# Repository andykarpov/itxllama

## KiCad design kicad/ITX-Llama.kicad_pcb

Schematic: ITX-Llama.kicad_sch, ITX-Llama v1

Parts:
BT1: CR2032; BT_BS-02-A1AJ006; LCSC C964745
C1, C2, C3, C4: 100uF; C_1210_3225Metric; LCSC C90143
C5, C10, C11, C31, C32, C43, C44, C45, C46, C47, C53, C61, C62, C76, C77, C159, C161, C167, C168, C169, C170, C171, C173: 47uF; C_0603_1608Metric; LCSC C140782
C6, C7, C8, C12, C13, C14, C16, C17, C18, C22, C25, C26, C29, C37, C38, C39, C40, C41, C42, C51, C54, C56, C57, C58, C59, C60, C63, C72, C73, C84, C85, C86, C87, C89, C90, C91, C92, C93, C94, C95, C96, C97, C98, C99, C100, C101, C102, C103, C104, C105, C106, C107, C108, C109, C110, C111, C112, C113, C114, C115, C116, C117, C118, C119, C120, C122, C123, C124, C129, C130, C131, C138, C144, C145, C146, C153, C156, C162, C163, C164, C165, C166, C182, C183, C184, C185, C186, C187, C188, C189, C190: 0.1uF; C_0603_1608Metric
C9, C33, C34, C52, C69, C74, C75, C134, C137, C143, C147, C148, C149, C158, C176: 10uF; C_0603_1608Metric
C15, C24, C28, C65, C66, C67, C78, C121, C132, C135, C150, C151, C152, C177, C178: 1uF; C_0603_1608Metric
C19, C23, C35, C36, C125, C126: 1nF; C_0603_1608Metric
C20, C21: 22pF; C_0603_1608Metric
C27: 47uF; C_0603_1608Metric
C30, C68: 2.7nF; C_0603_1608Metric
C48, C49, C50: 330pF; C_0603_1608Metric
C55, C64, C160: 10nF; C_0603_1608Metric
C70, C71: 0.33uF; C_0603_1608Metric
C79, C133, C136, C157: 470pF; C_0603_1608Metric
C80: 1nF; C_1812_4532Metric; Voltage min. 2kV; LCSC C106132
C81, C82, C83: 0.1uF; C_0603_1608Metric; LCSC C14663
C88, C154, C155: 4.7uF; C_0603_1608Metric
C127, C128: 5.6nF; C_0603_1608Metric
C139, C140: 2.2uF; C_0603_1608Metric
C141, C142: 2.2nF; C_0603_1608Metric
C172, C174, C175: 10uF; C_0603_1608Metric; LCSC C140782
C179: 0.1uF; C_0603_1608Metric; LCSC C107004
C180, C181: 30pF; C_0603_1608Metric; LCSC C107004
D1: RGB_LED; D_LED_D5.0mm-4_RGB; LCSC C417349
D2, D3, D4: 1N4148; D_SOD-323F; LCSC C2128
F1, F2, F5, F6, F7: F; Fuse_0603_1608Metric
F3, F4: F; Fuse_0603_1608Metric; LCSC C207017
FB1, FB2: 600Ω@100MHz; R_0603_1608Metric; LCSC C160977
FB3: 50Ω@100MHz; R_1206_3216Metric; LCSC C88997
FB4, FB5, FB6, FB7, FB8, FB9: 70Ω@100MHz; R_0603_1608Metric; LCSC C113031
H1, H2, H3, H4: H_HOLE; H_ATX_PERF
J1: ATX_POWER; J_ATX_5.5mm; LCSC C114125
J2: MICRO_SD; J_MicroSD_TF01A; LCSC C91145
J3: FRONT_PANEL; P_CONN_PANEL; LCSC C492421
J4: PS/2; J_PS2_KMDGX
J5: AGP_3.3V; J_TE_5145263-3
J6: CLICK_VOL; P_CONN_SPKR_VOL
J7: MSC; P_CONN_01X03
J8: COM1; J_DE9M; LCSC C141880
J9: INT_SPKR_VOL; P_CONN_SPKR_VOL
J10: SATA; J_SATA; LCSC C2926809
J11: SPEAKER; P_CONN_01X04; LCSC C492403
J12: MSD; P_CONN_01X03
J14: AUDIO; J_AUDIO_ABA-JAK-027-K24; LCSC C962118
J15: KBC; P_CONN_01X03
J16: KBD; P_CONN_01X03
J17: USB_ETH; J_USB_A_ETH_C3000093; LCSC C3000093
J18: USB_HID; J_USB_A_C456021; LCSC C456021
J19: HID_POWER; P_CONN_01X02
J20: FAN1; J_MOLEX_47053-1000; LCSC C240840
J21: FAN2; J_MOLEX_47053-1000; LCSC C240840
J22: GAMEPORT; J_DA15; LCSC C77835
J23: WAVETABLE; J_CONN_WAVETABLE; LCSC C2884022
J24: PI_ZERO2; J_CONN_RPI_SMD; LCSC C3975165
J25: POWER; P_CONN_01X03
J26: LEFT; P_CONN_01X03
J27: RIGHT; P_CONN_01X03
J28: COM2_TTL; P_CONN_01X03
J29: PI_2/3/4; J_CONN_RPI_SMD_PI3; LCSC C2884029
J30: FAN3; J_MOLEX_47053-1000; LCSC C240840
J31: FAN1_VDD; P_CONN_01X03
J32: FAN2_VDD; P_CONN_01X03
J33: FAN3_VDD; P_CONN_01X03
J34: CD_IN; J_CONN_CD_AUDIO; LCSC C41927
J35: D1_MINI; J_WEMOS_D1_MINI
J36: ESP_POWER; P_CONN_01X02
J38: J_TOSLINK_ZGY133T10; LCSC C277782
J39: LINE_L; P_CONN_01X03
J40: LINE_R; P_CONN_01X03
J41: EXT_SYNTH; J_CONN_02X10
J42: PI_I2C; P_CONN_01X04
J43: I2C; P_CONN_01X04_NO_3D
J46: RP_DEBUG; P_CONN_01X03
L1, L2: L_EMI_FILTER; L_EMI_FILTER_MCM2012B900GBE; LCSC C315725
L3, L4: L_EMI_FILTER; L_EMI_FILTER_MCM2012B900GBE
LOGO1: Llama_logo; LLAMA_LOGO
OUTLINE1: Outline; OUTLINE_PANELIZED
P1: P_SOM-128-EX; P_CONN_SOM-128-EX_FAN; LCSC C2881937
Q1, Q2, Q3, Q4, Q5, Q6, Q7: NPN; Q_BJT_SOT-23-3; LCSC C2146
Q8, Q9, Q10, Q11: Q_NMOS_GDS; Q_NFET_ENH_SOT-23-3; LCSC C255592
R1, R2, R3, R4, R5, R6, R27, R60, R61: 47k; R_0603_1608Metric
R7, R8, R9, R11, R12, R40, R53, R118: 33; R_0603_1608Metric
R10: 0; R_0603_1608Metric
R13, R20, R42, R57, R81, R82, R87, R88, R97, R100, R102, R110, R111, R112, R115, R120: 10k; R_0603_1608Metric
R14, R98, R101: 470; R_0603_1608Metric
R15, R16, R28, R62, R66, R67, R84, R85, R86, R89, R90, R91: 4.7k; R_0603_1608Metric
R17, R63: 600; R_0603_1608Metric
R18, R74, R75, R116: 330; R_0603_1608Metric
R19, R64: 2k; R_0603_1608Metric
R21, R22, R24, R25, R103, R104, R105, R106: 6.8k; R_0603_1608Metric
R23, R26, R29, R30, R31, R32, R33, R34, R35, R36, R37, R38, R41, R46, R47, R48, R49, R50, R51, R52, R54, R79, R80, R108, R121: 5.1k; R_0603_1608Metric
R39, R117: 200; R_0603_1608Metric
R43, R44, R55, R58, R78, R119: 1k; R_0603_1608Metric
R45, R56: 27; R_0603_1608Metric
R59, R94, R95, R96: 470; R_0805_2012Metric; LCSC C17710
R65: 1.43k; R_0603_1608Metric
R68, R69, R76, R77: 75; R_0603_1608Metric
R70, R71, R72, R73: 49.9; R_0603_1608Metric
R83, R107: 3.4k; R_0603_1608Metric
R92, R93: 2.2k; R_0603_1608Metric
R99: 20k; R_0603_1608Metric
R109: 22; R_0603_1608Metric
R113: 15.8k; R_0603_1608Metric
R114: 36k; R_0603_1608Metric
SP1, SP2: SPEAKER; SP; LCSC C252917
SW1: POWER; SW_B3FS-1010; LCSC C271750
SW2: RESET; SW_B3FS-1010; LCSC C271750
SW3: CH559_PRG; SW_B3FS-1010; LCSC C271750
T1: Pulse_H1102NL; T_PULSE_H1102NL; LCSC C18584
U1: MAX16054; U_TSOT-23-6; LCSC C79401
U2: U_74LVC1G04; U_SOT-23-5; LCSC C7827
U3: U_CS4237B-KQ; U_TQFP-100_14x14mm_P0.5mm_HandSoldering
U4: GD75232; U_TSSOP-20_4.4x6.5mm_P0.65mm; LCSC C543039
U5: U_MC33078; SOIC-8_3.9x4.9mm_P1.27mm; LCSC C108206
U6: PI7C9X118SL; U_LQFP-128_14x14mm_P0.4mm_EP
U7: AP7165; U_Diodes_SO-8EP; LCSC C460364
U8, U10, U13, U14: U_MIC5219-3.3YM5; U_SOT-23-5; LCSC C29613
U9: U_ATTINY84A; U_DIP-14_W7.62mm
U11: EMC2303; U_EMC2303; LCSC C621414
U12: PCM5102A; U_TSSOP-20_4.4x6.5mm_P0.65mm; LCSC C107671
U15: W25Q32JVSS; U_SOIC-8_5.23x5.23mm_P1.27mm
U16: U_74LVC1G126; U_SOT-23-5; LCSC C7834
U17: U_RP2040; U_QFN40P700X700X90-57N
X1: 16.9344MHz; X_Crystal_SMD_HC49S-MINI; LCSC C4944017
X2: 12MHz; X_SMD3225; LCSC C9002

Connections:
+1.8V: FB3.1, P1.A56 (VCC1.8_OUT)
+1.15V: C75.2, C153.2, FB6.1, FB7.1, R113.1, U7.7 (VOUT), U7.8 (VOUT)
+1.15V_VDDA: C101.2, C102.2, C155.2, FB7.2, U6.15 (VDDA), U6.18 (VDDA)
+1.15V_VDDC: C89.2, C90.2, C91.2, C92.2, C93.2, C94.2, C95.2, C96.2, C97.2, C98.2, C99.2, C100.2, C154.2, FB6.2, U6.7 (VDDCAUX), U6.30 (VDDC), U6.35 (VDDC), U6.45 (VDDC), U6.53 (VDDC), U6.62 (VDDC), U6.73 (VDDC), U6.81 (VDDC), U6.95 (VDDC), U6.105 (VDDC), U6.114 (VDDC), U6.127 (VDDC)
+3.3V: C3.1, C7.1, C12.1, C22.2, C74.2, C122.1, FB4.1, FB5.1, FB8.1, FB9.1, J1.1 (+3.3V), J1.2 (+3.3V), J1.12 (+3.3V), J1.13 (+3.3V), J2.4 (VDD), R1.1, R2.1, R3.1, R4.1, R5.1, R6.1, R74.1, R75.1, R79.1, R80.1, R84.2, R85.2, R86.2, R87.1, R88.1, R95.1, R102.1, R120.2, U2.5 (VCC), U3.45 (VD1), U7.1 (VIN), U7.2 (VIN), U7.4 (EN), U11.3 (VDD)
+3.3VSB: C156.2, C158.1, U9.1 (VCC), U10.5 (OUT)
+3.3V_118SL: C103.2, C104.2, C105.2, C106.2, C107.2, C108.2, C109.2, C110.2, C111.2, C112.2, C113.2, C114.2, C115.2, C116.2, C117.2, C118.2, C119.2, FB4.2, R33.2, R34.2, R36.1, R37.1, R38.1, R51.1, R52.1, R54.1, R108.2, R121.2, U6.2 (VAUX), U6.25 (VD33), U6.38 (VD33), U6.50 (VD33), U6.55 (VD33), U6.58 (VD33), U6.66 (VD33), U6.72 (VD33), U6.77 (VD33), U6.82 (VD33), U6.87 (VD33), U6.91 (VD33), U6.101 (VD33), U6.107 (VD33), U6.112 (VD33), U6.118 (VD33), U6.123 (VD33)
+3.3V_PCM_A: C137.1, C143.1, C144.1, U12.8 (AVDD), U14.5 (OUT)
+3.3V_PCM_D: C134.1, C138.1, C145.1, C147.1, C148.1, U12.1 (CPVDD), U12.17 (XSMT), U12.20 (DVDD), U13.5 (OUT)
+3.3V_VDDA: C88.2, C120.2, FB5.2, U6.10 (VDDA33)
+5VA: C25.1, C72.1, FB1.2, U3.81 (VA), U5.8 (VCC)
+5VFILT: C13.2, C14.2, C16.2, C18.2, FB2.2, U3.17 (VDF1), U3.54 (VDF4), U3.65 (VDF2), U3.98 (VDF3)
+5VSB: C8.2, C121.1, D1.2 (A), J1.9 (+5VSB), R59.1, U1.6 (VCC), U10.1 (IN), U10.3 (EN)
+12V: C1.1, C51.2, C52.2, C172.1, C174.1, C175.1, J1.10 (+12V), J1.11 (+12V), J5.A1 (+12V), J23.18 (+12V), J31.1, J32.1, J33.1, R96.1, U4.1 (VDD)
-12V: C4.2, J1.14 (-12V), J23.22 (-12V), U4.10 (VSS)
/3.3V_MIDI_OUT: J24.10 (BCM15/RDX), J29.10 (BCM15/RDX), R99.1, R100.2
/A0: P1.B3 (GP70), U3.25 (SA0)
/A1: P1.B4 (GP71), U3.26 (SA1)
/A2: P1.B5 (GP72), U3.27 (SA2)
/A3: P1.B6 (GP73), U3.28 (SA3)
/A4: P1.B7 (GP74), U3.29 (SA4)
/A5: P1.B8 (GP75), U3.30 (SA5)
/A6: P1.B9 (GP76), U3.31 (SA6)
/A7: P1.B10 (GP77), U3.32 (SA7)
/A8: P1.B11 (GP60), U3.33 (SA8)
/A9: P1.B12 (GP61), U3.34 (SA9)
/A10: P1.B13 (GP62), U3.35 (SA10)
/A11: P1.B14 (GP63), U3.36 (SA11)
/A12: P1.B15 (GP64), U3.94 (SA12)
/A13: P1.B16 (GP65), U3.93 (SA13)
/A14: P1.B17 (GP66), U3.92 (SA14)
/A15: P1.B18 (GP67), U3.91 (SA15)
/AD_STB0: J5.B59 (AD_STB0), R26.2
/AD_STB1: J5.B32 (AD_STB1), R29.2
/AEN: P1.B33 (GP44), U3.39 (AEN)
/AUDIO_L_PI: C141.2, J26.3, R98.2
/AUDIO_L_WT: J23.24 (AUDIO_L), J26.1
/AUDIO_R_PI: C142.2, J27.3, R101.2
/AUDIO_R_WT: J23.20 (AUDIO_R), J27.1
/AUDIO_VREF: R60.2, U3.78 (VREF)
/BOOTSEL: R43.2, SW3.1 (A)
/CTS1: P1.A10 (GP07), U4.14 (RY4)
/D0: P1.B47 (GP20), U3.41 (SD0)
/D1: P1.B48 (GP21), U3.42 (SD1)
/D2: P1.B49 (GP22), U3.43 (SD2)
/D3: P1.B50 (GP23), U3.44 (SD3)
/D4: P1.B51 (GP24), U3.47 (SD4)
/D5: P1.B52 (GP25), U3.48 (SD5)
/D6: P1.B53 (GP26), U3.49 (SD6)
/D7: P1.B54 (GP27), U3.50 (SD7)
/DCD1: P1.A3 (GP00), U4.19 (RY1)
/DRQ1: P1.B27 (GP56), U3.51 (DRQB(DRQ1*))
/DSR1: P1.A9 (GP06), U4.18 (RY2)
/DTR1: P1.A8 (GP05), U4.13 (DA3)
/FM_A0: J41.18, U3.14 (SCL/XA0)
/FM_A1: J41.16, U3.13 (XA1)
/FM_D0: J41.12, U3.8 (SDA/XD0)
/FM_D1: J41.11, U3.7 (XD1/SCLK)
/FM_D2: J41.10, U3.6 (XD2/SDIN)
/FM_D3: J41.9, U3.5 (XD3/SDOUT)
/FM_D4: J41.8, U3.4 (XD4/FSYNC)
/FM_D5: J41.7, U3.3 (XD5/MCLK)
/FM_D6: J41.6, U3.2 (XD6/LRCK)
/FM_D7: J41.5, U3.1 (XD7/SDATA)
/FM_SYNTH_L: C24.2, J41.1
/FM_SYNTH_R: C28.2, J41.2
/HDD_LED+: J3.1, R116.2
/HDD_LED-: J3.2, Q6.3 (C)
/HID_VCC: C78.1, F5.1, F6.1, J19.2, U8.1 (IN), U8.3 (EN)
/I2S_BCLK: J24.12 (BCM18/PWM0), J29.12 (BCM18/PWM0), U12.13 (BCK)
/I2S_DATA: J24.40 (BCM21/SCLK), J29.40 (BCM21/SCLK), U12.14 (DIN)
/I2S_LRCLK: J24.35 (BCM19/MISO), J29.35 (BCM19/MISO), U12.15 (LRCK)
/INT_MIDI_L: J26.2, J39.1
/INT_MIDI_R: J27.2, J40.1
/IOCHRDY: P1.B34 (GP45), U3.40 (IOCHRDY)
/IRQ7: P1.B21 (GP50), U3.23 ((INT7*)IRQB)
/JAB1: C126.2, J22.2, R91.2, U3.70 (JAB1)
/JAB2: C125.2, J22.7, R90.2, U3.61 (JAB2)
/JACX: C128.2, R92.2, U3.68 (JACX)
/JACX_: J22.3, R92.1
/JACY: C127.2, R93.2, U3.63 (JACY)
/JACY_: J22.6, R93.1
/KBCLK: J15.2, P1.A12 (GP91), R66.1
/KBDATA: J16.2, P1.A14 (GP93), R67.1
/LAN_RD+: P1.A54 (LAN_RX+), R72.2, T1.6 (RD+)
/LAN_RD-: P1.A52 (LAN_RX-), R73.2, T1.8 (RD-)
/LAN_TD+: P1.A53 (LAN_TX+), R70.2, T1.1 (TD+)
/LAN_TD-: P1.A51 (LAN_TX-), R71.2, T1.3 (TD-)
/LIN: J14.10, J14.11, J39.3
/LINE_IN_L: J39.2, R21.1
/LINE_IN_R: J40.2, R24.1
/LMIC: C73.1, J14.2, J14.3
/LOUT: C34.2, J14.6, J14.7
/M66EN: R121.1, U6.102 (M66EN)
/MIDI_IN: J22.15, R89.2, U3.59 (MIDIN)
/MIDI_OUT: J22.12, J23.4 (MIDI_IN), R100.1, U3.60 (MIDOUT)
/MSCLK: J7.2, P1.A13 (GP92), R15.1
/MSDATA: J12.2, P1.A15 (GP94), R16.1
/PAR: J5.A50 (PAR), U6.94 (PAR)
/PCI_AD0: J5.A65 (AD[0]), U6.64 (AD0)
/PCI_AD1: J5.B65 (AD[1]), U6.67 (AD1)
/PCI_AD2: J5.A63 (AD[2]), U6.69 (AD2)
/PCI_AD3: J5.B63 (AD[3]), U6.68 (AD3)
/PCI_AD4: J5.A62 (AD[4]), U6.70 (AD4)
/PCI_AD5: J5.B62 (AD[5]), U6.71 (AD5)
/PCI_AD6: J5.A60 (AD[6]), U6.74 (AD6)
/PCI_AD7: J5.B60 (AD[7]), U6.75 (AD7)
/PCI_AD8: J5.B57 (AD[8]), U6.78 (AD8)
/PCI_AD9: J5.A56 (AD[9]), U6.79 (AD9)
/PCI_AD10: J5.B56 (AD[10]), U6.80 (AD10)
/PCI_AD11: J5.A54 (AD[11]), U6.83 (AD11)
/PCI_AD12: J5.B54 (AD[12]), U6.85 (AD12)
/PCI_AD13: J5.A53 (AD[13]), U6.86 (AD13)
/PCI_AD14: J5.B53 (AD[14]), U6.88 (AD14)
/PCI_AD15: J5.A51 (AD[15]), U6.90 (AD15)
/PCI_AD16: J5.A39 (AD[16]), U6.104 (AD16)
/PCI_AD17: J5.B38 (AD[17]), U6.103 (AD17)
/PCI_AD18: J5.A38 (AD[18]), U6.106 (AD18)
/PCI_AD19: J5.B36 (AD[19]), U6.108 (AD19)
/PCI_AD20: J5.A36 (AD[20]), U6.109 (AD20)
/PCI_AD21: J5.B35 (AD[21]), U6.110 (AD21)
/PCI_AD22: J5.A35 (AD[22]), U6.111 (AD22)
/PCI_AD23: J5.B33 (AD[23]), U6.113 (AD23)
/PCI_AD24: J5.A30 (AD[24]), U6.117 (AD24)
/PCI_AD25: J5.B30 (AD[25]), U6.119 (AD25)
/PCI_AD26: J5.A29 (AD[26]), U6.120 (AD26)
/PCI_AD27: J5.B29 (AD[27]), U6.122 (AD27)
/PCI_AD28: J5.A27 (AD[28]), U6.121 (AD28)
/PCI_AD29: J5.B27 (AD[29]), U6.124 (AD29)
/PCI_AD30: J5.A26 (AD[30]), U6.126 (AD30)
/PCI_AD31: J5.B26 (AD[31]), U6.125 (AD31)
/PCI_CLK0: J5.B7 (CLK), R109.1
/PE0_CLK+: C85.2, P1.A45 (PE0_CLK-)
/PE0_CLK+_: C85.1, U6.13 (REFCLKP)
/PE0_CLK-: C84.2, P1.A47 (PE0_CLK+)
/PE0_CLK-_: C84.1, U6.12 (REFCLKN)
/PE0_RX+: C87.2, P1.A44 (PE0_RX+)
/PE0_RX+_: C87.1, U6.17 (TP)
/PE0_RX-: C86.2, P1.A42 (PE0_RX-)
/PE0_RX-_: C86.1, U6.16 (TN)
/PE0_TX+: P1.A41 (PE0_TX-), U6.21 (RP)
/PE0_TX-: P1.A43 (PE0_TX+), U6.20 (RN)
/PI7_SCL: R80.2, U6.3 (SCL)
/PI7_SDA: R79.2, U6.5 (SDA)
/PI_SCL: J24.5 (BCM3/SCL), J29.5 (BCM3/SCL), J42.3 (SCL)
/PI_SDA: J24.3 (BCM2/SDA), J29.3 (BCM2/SDA), J42.4 (SDA)
/PS2_KBCLK: J4.A5 (KBCLK), J15.3
/PS2_KBDATA: J4.A1 (KBDATA), J16.3
/PS2_MSCLK: J4.B5 (MSCLK), J7.3
/PS2_MSDATA: J4.B1 (MSDATA), J12.3
/PWM1: J20.4 (PWM), U11.5 (PWM1)
/PWM2: J21.4 (PWM), U11.7 (PWM2)
/PWM3: J30.4 (PWM), U11.11 (PWM3)
/PWM_CLICK: R119.1, U9.8 (PCINT5/OC1B/PA5)
/PWM_GREEN: R82.1, U9.10 (PCINT3/PA3)
/PWM_HDD: R115.1, U9.12 (PCINT1/PA1)
/PWM_PWR: R20.1, U9.13 (PCINT0/PA0)
/PWM_RED: R81.1, U9.11 (PCINT2/PA2)
/PWR_LED+: J3.8, R18.2
/PWR_LED-: J3.7, Q7.3 (C)
/QSPI_CS: R42.1, R43.1, U15.1 (~CS), U17.56 (QSPI_CSN)
/QSPI_SCK: U15.6 (CLK), U17.52 (QSPI_SCLK)
/QSPI_SD0: U15.5 (DI(IO0)), U17.53 (QSPI_SD0)
/QSPI_SD1: U15.2 (DO(IO1)), U17.55 (QSPI_SD1)
/QSPI_SD2: U15.3 (IO2), U17.54 (QSPI_SD2)
/QSPI_SD3: U15.7 (IO3), U17.51 (QSPI_SD3)
/RI1: P1.A6 (GP03), U4.12 (RY5)
/RIN: J14.12, J14.13, J40.3
/RMIC: J14.4, J14.5, R64.2
/ROUT: C33.2, J14.8, J14.9
/RP_RX: J46.3, U17.16 (GPIO13)
/RP_TX: J46.1, U17.15 (GPIO12)
/RSTDRV: U2.4, U3.90 (RESDRV)
/RS_CTS1: J8.8, U4.7 (RA4)
/RS_DCD1: J8.1, U4.2 (RA1)
/RS_DSR1: J8.6, U4.3 (RA2)
/RS_DTR1: C50.2, J8.4, U4.8 (DY3)
/RS_RI1: J8.9, U4.9 (RA5)
/RS_RTS1: C48.2, J8.7, U4.5 (DY1)
/RS_RX1: J8.2, U4.4 (RA3)
/RS_TX1: C49.2, J8.3, U4.6 (DY2)
/RTS1: P1.A5 (GP02), U4.16 (DA1)
/RX1: P1.A7 (GP04), U4.17 (RY3)
/RX2: J28.3, J35.16 (TX/GPIO1), P1.B63 (GP16), U9.2 (PB0/PCINT8)
/SATA_RX+: J10.6 (B+), P1.A40 (SATA_RX+)
/SATA_RX-: J10.5 (B-), P1.A38 (SATA_RX-)
/SATA_TX+: J10.2 (A+), P1.A39 (SATA_TX+)
/SATA_TX-: J10.3 (A-), P1.A37 (SATA_TX-)
/SB_STB: J5.B18 (SB_STB), R30.2
/SD_CD: J2.9 (CD), P1.A63 (GP86), R1.2
/SD_CLK: P1.A60 (GP83), R10.2
/SD_CMD: P1.A59 (GP82), R9.2, U9.5 (PB2/PCINT10/INT0/OC0A)
/SD_DAT0: P1.A61 (GP84), R11.2, U9.6 (PA7/PCINT7/OC0B)
/SD_DAT1: P1.A62 (GP85), R12.2
/SD_DAT2: P1.A57 (GP80), R7.2
/SD_DAT3: P1.A58 (GP81), R8.2
/SPDIF_OUT: U3.67 (JBCX*/SDOUT), U16.2
/SPKR: P1.B58 (GP11), R27.1, R44.1, R55.1
/TACH1: J20.3 (TACH), R88.2, U11.6 (TACH1)
/TACH2: J21.3 (TACH), R87.2, U11.8 (TACH2)
/TACH3: J30.3 (TACH), R102.2, U11.12 (TACH3)
/TX1: P1.A4 (GP01), U4.15 (DA2)
/TX2: J28.1, J35.15 (RX/GPIO3), P1.B61 (GP14), U9.3 (PB1/PCINT9)
/USBD1+: L1.3, P1.A23 (USBD1+)
/USBD1-: L1.2, P1.A21 (USBD1-)
/USBD2+: L2.3, P1.A24 (USBD2+)
/USBD2-: L2.2, P1.A22 (USBD2-)
/USBDX1+: J17.U3 (D1+), L1.4
/USBDX1-: J17.U2 (D1-), L1.1
/USBDX2+: J17.U7 (D2+), L2.4
/USBDX2-: J17.U6 (D2-), L2.1
/USBHID1+: L3.3, R45.1
/USBHID1-: L3.2, R56.1
/USBHID2+: L4.3, U17.36 (GPIO24)
/USBHID2-: L4.2, U17.37 (GPIO25)
/USBHIDX1+: J18.7 (D2+), L3.4
/USBHIDX1-: J18.6 (D2-), L3.1
/USBHIDX2+: J18.3 (D1+), L4.4
/USBHIDX2-: J18.2 (D1-), L4.1
/USB_KBCLK_HV: J15.1, Q9.2 (D)
/USB_KBCLK_LV: Q9.3 (S), R110.2, U17.5 (GPIO3)
/USB_KBDATA_HV: J16.1, Q8.2 (D)
/USB_KBDATA_LV: Q8.3 (S), R97.2, U17.4 (GPIO2)
/USB_MSCLK_HV: J7.1, Q10.2 (D)
/USB_MSCLK_LV: Q10.3 (S), R111.2, U17.7 (GPIO5)
/USB_MSDATA_HV: J12.1, Q11.2 (D)
/USB_MSDATA_LV: Q11.3 (S), R112.2, U17.6 (GPIO4)
/V86_SCL: J43.3 (SCL), P1.B62 (GP15), R85.1, U9.9 (PCINT4/SCL/PA4), U11.2 (SMCLK)
/V86_SDA: J43.4 (SDA), P1.B60 (GP13), R84.1, U9.7 (PA6/PCINT6/OCA1A/SDA), U11.1 (SMDATA)
/VBATT: BT1.1 (+), P1.A55 (VBATT)
/X_SD_CLK: J2.5 (CLK), R10.1
/X_SD_CMD: J2.3 (CMD), R4.2, R9.1
/X_SD_DAT0: J2.7 (DAT0), R3.2, R11.1
/X_SD_DAT1: J2.8 (DAT1), R2.2, R12.1
/X_SD_DAT2: J2.1 (DAT2), R6.2, R7.1
/X_SD_DAT3: J2.2 (DAT3/CD), R5.2, R8.1
/~BRESET: J23.26 (~RESET), J41.4, U3.15 (~BRESET)
/~CBE0: J5.A57 (~C/BE[0]), U6.76 (~CBE0)
/~CBE1: J5.B51 (~C/BE[1]), U6.89 (~CBE1)
/~CBE2: J5.B39 (~C/BE[2]), U6.99 (~CBE2)
/~CBE3: J5.A33 (~C/BE[3]), U6.116 (~CBE3)
/~DACK1: P1.B28 (GP57), U3.56 (~DACKB(~DACK1*))
/~DEVSEL: J5.B46 (~DEVSEL), R49.2, U6.98 (~DEVSEL)
/~FM_CS: J41.13, U3.9 (~SCS/~UP)
/~FM_RD: J41.14, U3.10 (~XIOR)
/~FM_WR: J41.15, U3.11 (~XIOW)
/~FRAME: J5.A41 (~FRAME), R46.2, U6.63 (~FRAME)
/~GNT0: J5.A8 (~GNT), R41.2, U6.37 (~GNT0)
/~INTA: J5.A6 (~INTA), R31.2, U6.36 (~INTA)
/~INTB: J5.B6 (~INTB), R32.2, U6.43 (~INTB)
/~INTC: R33.1, U6.57 (~INTC)
/~INTD: R34.1, U6.60 (~INTD)
/~IOR: P1.B40 (GP31), U3.37 (~IOR)
/~IOW: P1.B39 (GP30), U3.38 (~IOW)
/~IRDY: J5.B41 (~IRDY), R48.2, U6.97 (~IRDY)
/~LAN_DUPLEX: J17.D2, P1.B57 (GP10)
/~LAN_LINK_ACK: J17.D4, P1.B59 (GP12)
/~LOCK: R51.2, U6.93 (~LOCK)
/~PCIE_RST: P1.A46 (~PCIRST), U2.2, U6.29 (~PERST)
/~PCI_RST: J5.A7 (~RST), U6.46 (~RESET)
/~PERR: R52.2, U6.92 (~PERR)
/~PIPE: J5.A12 (~PIPE), R23.2
/~PS_ON: J1.16 (~PS_ON), U1.4 (~OUT)
/~PWR_SW: J3.6, SW1.2 (B), U1.1 (IN)
/~REQ0: J5.B8 (~REQ), R35.2, U6.31 (~REQ0)
/~RST_SIG: C9.1, P1.A48 (~RESET), R14.1
/~RST_SW: J3.3, R13.2, R14.2, SW2.2 (B)
/~SERR: R54.2, U6.61 (~SERR)
/~STOP: J5.A47 (~STOP), R50.2, U6.96 (~STOP)
/~TRDY: J5.A46 (~TRDY), R47.2, U6.100 (~TRDY)
GND: BT1.2 (-), C1.2, C2.2, C3.2, C4.1, C5.2, C6.2, C7.2, C8.1, C9.2, C10.1, C11.1, C12.2, C13.1, C14.1, C15.2, C16.1, C17.2, C18.1, C19.2, C20.1, C21.1, C22.1, C23.2, C25.2, C26.1, C27.1, C30.2, C31.2, C32.2, C35.2, C36.2, C37.1, C38.1, C39.1, C40.1, C41.1, C42.1, C43.2, C44.2, C45.2, C46.2, C47.2, C48.1, C49.1, C50.1, C51.1, C52.1, C53.2, C54.1, C55.2, C56.1, C57.1, C58.1, C59.1, C60.1, C61.2, C62.2, C63.1, C64.2, C67.1, C69.2, C72.2, C74.1, C75.1, C76.2, C77.2, C78.2, C79.2, C80.1, C81.1, C82.1, C83.1, C88.1, C89.1, C90.1, C91.1, C92.1, C93.1, C94.1, C95.1, C96.1, C97.1, C98.1, C99.1, C100.1, C101.1, C102.1, C103.1, C104.1, C105.1, C106.1, C107.1, C108.1, C109.1, C110.1, C111.1, C112.1, C113.1, C114.1, C115.1, C116.1, C117.1, C118.1, C119.1, C120.1, C121.2, C122.2, C123.1, C124.1, C125.1, C126.1, C127.1, C128.1, C129.1, C130.1, C131.1, C132.2, C133.2, C134.2, C135.2, C136.2, C137.2, C138.2, C139.1, C141.1, C142.1, C143.2, C144.2, C145.2, C146.1, C147.2, C148.2, C149.1, C153.1, C154.1, C155.1, C156.1, C157.2, C158.2, C159.2, C160.2, C161.2, C162.1, C163.2, C164.1, C165.1, C166.1, C167.2, C168.2, C169.2, C170.2, C171.2, C172.2, C173.2, C174.2, C175.2, C176.2, C177.2, C178.2, C179.1, C180.2, C181.2, C182.1, C183.1, C184.1, C185.1, C186.1, C187.1, C188.1, C189.1, C190.1, H1.1, H2.1, H3.1, H4.1, J1.3 (GND), J1.5 (GND), J1.7 (GND), J1.15 (GND), J1.17 (GND), J1.18 (GND), J1.19 (GND), J1.24 (GND), J2.6 (VSS), J2.S (Shield), J3.4, J3.5, J4.A3 (GND), J4.B3 (GND), J4.S (SHIELD), J5.A3 (RES_GND), J5.A5 (GND), J5.A13 (GND), J5.A19 (GND), J5.A31 (GND), J5.A37 (GND), J5.A43 (GND), J5.A49 (GND), J5.A55 (GND), J5.A61 (GND), J5.B5 (GND), J5.B13 (GND), J5.B19 (GND), J5.B31 (GND), J5.B37 (GND), J5.B43 (GND), J5.B49 (GND), J5.B55 (GND), J5.B61 (GND), J8.5, J8.10 (GND), J8.11 (GND), J10.1 (GND), J10.4 (GND), J10.7 (GND), J11.3, J14.1, J17.U4 (GND1), J17.U8 (GND2), J18.4 (GND1), J18.8 (GND2), J18.S (Shield), J20.1 (GND), J21.1 (GND), J22.4, J22.5, J22.S (SHIELD), J23.1 (GND), J23.3 (GND), J23.5 (GND), J23.7 (GND), J23.9 (GND), J23.11 (GND), J23.15 (AGND), J23.17 (AGND), J23.19 (AGND), J23.21 (AGND), J23.23 (AGND), J23.25 (AGND), J24.6 (GND), J24.9 (GND), J24.14 (GND), J24.20 (GND), J24.25 (GND), J24.30 (GND), J24.34 (GND), J24.39 (GND), J28.2, J29.6 (GND), J29.9 (GND), J29.14 (GND), J29.20 (GND), J29.25 (GND), J29.30 (GND), J29.34 (GND), J29.39 (GND), J30.1 (GND), J35.10 (GND), J38.3 (GND), J41.3, J41.20, J42.1 (GND), J43.1 (GND), J46.2, P1.A2 (GND), P1.A19 (GND), P1.A20 (GND), P1.A25 (AGND), P1.A26 (AGND), P1.A35 (GND), P1.A36 (GND), P1.A49 (GND), P1.A50 (GND), P1.A64 (GP87), P1.B19 (GND), P1.B20 (GND), P1.B37 (GND), P1.B38 (GND), P1.B55 (GND), P1.B56 (GND), Q1.2 (E), Q2.2 (E), Q3.2 (E), Q4.2 (E), Q5.2 (E), Q6.2 (E), Q7.2 (E), R22.2, R25.2, R28.2, R59.2, R78.2, R94.2, R95.2, R96.2, R99.2, R105.2, R106.2, R107.2, R114.2, SW1.1 (A), SW2.1 (A), SW3.2 (B), U1.2 (GND), U1.3 (CLEAR), U2.3 (GND), U3.18 (SGND1), U3.46 (DGND1), U3.53 (SGND4), U3.66 (SGND2), U3.71 (TEST), U3.80 (AGND), U3.97 (SGND3), U4.11 (GND), U5.4 (GND), U6.6 (VSS), U6.11 (VSS), U6.14 (VSS), U6.19 (VSS), U6.22 (VSS), U6.23 (TM1), U6.42 (VSS), U6.44 (CLKIN), U6.65 (VSS), U6.84 (VSS), U6.115 (VSS), U6.128 (TM0), U6.129 (EPAD), U7.5 (GND), U7.9 (GND), U8.2 (GND), U9.14 (GND), U10.2 (GND), U11.9 (CLK), U11.13 (GND), U12.3 (CPGND), U12.9 (AGND), U12.10 (DEMP), U12.11 (FLT), U12.12 (SCK), U12.16 (FMT), U12.19 (DGND), U13.2 (GND), U14.2 (GND), U15.4 (GND), U16.3 (GND), U17.19 (TESTEN), U17.57 (GND), X2.2, X2.4
unnamed: C10.2, F1.2, J4.A4 (VCC)
unnamed: C11.2, F2.2, J4.B4 (VCC)
unnamed: C29.2, C30.1, R27.2, R28.1
unnamed: C65.2, R24.2, R25.1
unnamed: C66.2, R21.2, R22.1
unnamed: C68.1, C70.1, C71.1, R62.1, U5.7
unnamed: C69.1, R63.2
unnamed: C80.2, R68.1, R69.1, R76.1, R77.1
unnamed: C82.2, R70.1, R71.1
unnamed: C83.2, R72.1, R73.1
unnamed: C123.2, F7.1, J22.1, J22.8, J22.9
unnamed: C150.2, R104.1, R105.1
unnamed: C151.2, R103.1, R106.1
unnamed: C152.2, R83.1, R107.1
unnamed: C180.1, R58.2, X2.3
unnamed: D1.3 (GK), R19.2
unnamed: D1.1 (RK), R17.2
unnamed: D2.2 (A), J9.2, SP1.2
unnamed: D3.2 (A), J11.1, R53.1
unnamed: D4.2 (A), J6.2, SP2.2
unnamed: J6.1, R117.2
unnamed: J6.3, R118.2
unnamed: J9.1, R39.2
unnamed: J9.3, R40.2
unnamed: J17.D1, R74.2
unnamed: J17.D3, R75.2
unnamed: J17.J4, J17.J5, R76.2
unnamed: J17.J7, J17.J8, R77.2
unnamed: C31.1, F3.2, J17.U1 (VBUS1)
unnamed: C32.1, F4.2, J17.U5 (VBUS2)
unnamed: C76.1, F5.2, J18.1 (VBUS1)
unnamed: C77.1, F6.2, J18.5 (VBUS2)
unnamed: J20.2 (VDD), J31.2
unnamed: J21.2 (VDD), J32.2
unnamed: J30.2 (VDD), J33.2
unnamed: J34.1, R103.2
unnamed: J34.2, J34.3, R83.2
unnamed: J34.4, R104.2
unnamed: C161.1, J35.9 (5V), J36.2
unnamed: J38.1 (VIN), U16.4
unnamed: Q1.1 (B), R44.2
unnamed: C55.1, Q1.3 (C), R39.1, R40.1
unnamed: Q2.1 (B), R55.2
unnamed: C64.1, Q2.3 (C), R53.2
unnamed: Q3.1 (B), R119.2
unnamed: C160.1, Q3.3 (C), R117.1, R118.1
unnamed: Q4.1 (B), R81.2
unnamed: Q4.3 (C), R17.1
unnamed: Q5.1 (B), R82.2
unnamed: Q5.3 (C), R19.1
unnamed: Q6.1 (B), R115.2
unnamed: Q7.1 (B), R20.2
unnamed: C81.2, FB3.2, T1.2 (C_TD), T1.7 (C_RD)
unnamed: R68.2, T1.10 (C_RX)
unnamed: R69.2, T1.15 (C_TX)
unnamed: J17.J3, T1.11 (RX+)
unnamed: J17.J6, T1.9 (RX-)
unnamed: J17.J1, T1.16 (TX+)
unnamed: J17.J2, T1.14 (TX-)
unnamed: C152.1, U3.96 (CMAUX2)
unnamed: C66.1, U3.75 (LAUX1)
unnamed: C150.1, U3.85 (LAUX2)
unnamed: C23.1, U3.77 (LFILT)
unnamed: C24.1, U3.87 (LLINE)
unnamed: C70.2, U3.83 (LMIC)
unnamed: C34.1, C35.1, U3.73 (LOUT)
unnamed: C29.1, U3.88 (MIN)
unnamed: C65.1, U3.74 (RAUX1)
unnamed: C151.1, U3.84 (RAUX2)
unnamed: C15.1, C17.1, U3.79 (REFFLT)
unnamed: C19.1, U3.76 (RFILT)
unnamed: C28.1, U3.86 (RLINE)
unnamed: C71.2, U3.82 (RMIC)
unnamed: C33.1, C36.1, U3.72 (ROUT)
unnamed: C21.2, U3.100 (XTALI), X1.2
unnamed: C20.2, U3.99 (XTALO), X1.1
unnamed: C67.2, R60.1, U5.3 (+)
unnamed: R61.1, R64.1, U5.1, U5.2 (-)
unnamed: C73.2, R61.2, U5.5 (+)
unnamed: C68.2, R62.2, R63.1, U5.6 (-)
unnamed: R109.2, U6.59 (CLKOUT0)
unnamed: R65.2, U6.9 (REXTN)
unnamed: R65.1, U6.8 (REXTP)
unnamed: R78.1, U6.24 (TMS)
unnamed: R108.1, U6.1 (~PME)
unnamed: R36.2, U6.32 (~REQ1)
unnamed: R37.2, U6.34 (~REQ2)
unnamed: R38.2, U6.33 (~REQ3)
unnamed: R113.2, R114.1, U7.6 (FB)
unnamed: C79.1, U8.4 (BYP)
unnamed: R120.1, U9.4 (PB3/PCINT11/~RESET)
unnamed: C157.1, U10.4 (BYP)
unnamed: R86.1, U11.4 (ADDR_SEL)
unnamed: C140.2, U12.4 (CAPM)
unnamed: C140.1, U12.2 (CAPP)
unnamed: C146.2, C149.2, U12.18 (LDOO)
unnamed: R98.1, U12.6 (OUTL)
unnamed: R101.1, U12.7 (OUTR)
unnamed: C139.2, U12.5 (VNEG)
unnamed: C133.1, U13.4 (BYP)
unnamed: C136.1, U14.4 (BYP)
unnamed: R57.2, U17.26 (RUN)
unnamed: R56.2, U17.46 (USB_DM)
unnamed: R45.2, U17.47 (USB_DP)
unnamed: C181.1, U17.20 (XIN), X2.1
unnamed: R58.1, U17.21 (XOUT)
RP_1.1V: C177.1, C189.2, C190.2, U17.23 (DVDD), U17.45 (VREG_VOUT), U17.50 (DVDD)
RP_3.3V: C176.1, C178.1, C179.2, C182.2, C183.2, C184.2, C185.2, C186.2, C187.2, C188.2, Q8.1 (G), Q9.1 (G), Q10.1 (G), Q11.1 (G), R42.2, R57.1, R97.1, R110.1, R111.1, R112.1, U8.5 (OUT), U15.8 (VCC), U17.1 (IOVDD), U17.10 (IOVDD), U17.22 (IOVDD), U17.33 (IOVDD), U17.42 (IOVDD), U17.43 (ADC_AVDD), U17.44 (VREG_VIN), U17.48 (USB_VDD), U17.49 (IOVDD)
VCC: C2.1, C5.1, C6.1, C26.2, C27.2, C37.2, C124.2, C163.1, C171.1, D2.1 (K), D3.1 (K), D4.1 (K), F1.1, F2.1, F3.1, F4.1, F7.2, FB1.1, FB2.1, J1.4 (+5V), J1.6 (+5V), J1.21 (+5V), J1.22 (+5V), J1.23 (+5V), J5.B2 (+5V), J5.B3 (+5V), J11.4, J19.1, J25.2, J31.3, J32.3, J33.3, J36.1, J38.2 (VCC), J41.17, J43.2 (VCC), P1.B1 (VCC), P1.B2 (VCC), R13.1, R15.2, R16.2, R18.1, R66.2, R67.2, R89.1, R90.1, R91.1, R94.1, R116.1, SP1.1, SP2.1, U4.20 (VCC), U16.1 (OE), U16.5 (VCC)
VCC_3V3_AGP: C61.1, C62.1, C63.2, C129.2, C130.2, C131.2, C159.1, C162.2, C164.2, C165.2, C166.2, C167.1, C168.1, C173.1, FB8.2, J5.A9 (VCC_3.3V), J5.A16 (VCC_3.3V), J5.A28 (VCC_3.3V), J5.A45 (VCC_3.3V), J5.B9 (VCC_3.3V), J5.B16 (VCC_3.3V), J5.B28 (VCC_3.3V), J5.B45 (VCC_3.3V)
VCC_PI: C132.1, C135.1, J24.2 (5v), J24.4 (5v), J25.3, J29.2 (5v), J29.4 (5v), J42.2 (VCC), U13.1 (IN), U13.3 (EN), U14.1 (IN), U14.3 (EN)
VCC_VIO_AGP: C38.2, C39.2, C40.2, C41.2, C42.2, C43.1, C44.1, C45.1, C46.1, C47.1, C53.1, C54.2, C56.2, C57.2, C58.2, C59.2, C60.2, C169.1, C170.1, FB9.2, J5.A34 (Vddq3.3), J5.A40 (Vddq3.3), J5.A52 (Vddq3.3), J5.A58 (Vddq3.3), J5.A64 (Vddq3.3), J5.B34 (Vddq3.3), J5.B40 (Vddq3.3), J5.B47 (Vddq3.3), J5.B52 (Vddq3.3), J5.B58 (Vddq3.3), J5.B64 (Vddq3.3), R23.1, R26.1, R29.1, R30.1, R31.1, R32.1, R35.1, R41.1, R46.1, R47.1, R48.1, R49.1, R50.1
VCC_WT: J23.6 (VCC), J23.10 (VCC), J23.14 (VCC), J25.1

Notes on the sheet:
LED CONTROL
SATA
POWER, RESET, FRONT PANEL
NOTE: ~{RST_SIG} is a CPU input ~{PCIE_RST} is a CPU output
FAN CONTROL
WAVETABLE, PI
MICRO-SD, WIFI
SPEAKERS
Next to ADC_AVDD
AUDIO, GAMEPORT
USB, ETHERNET
One cap next to each IOVDD pin
Bleeder resistors
AGP SLOT
Make sure that the external synth module outputs max 1Vrms
SD_WP
Next to each DVDD pin
DECORATION
BATTERY
SERIAL
PCI BRIDGE
SYSTEM-ON-MODULE
MECHANICAL
PS/2

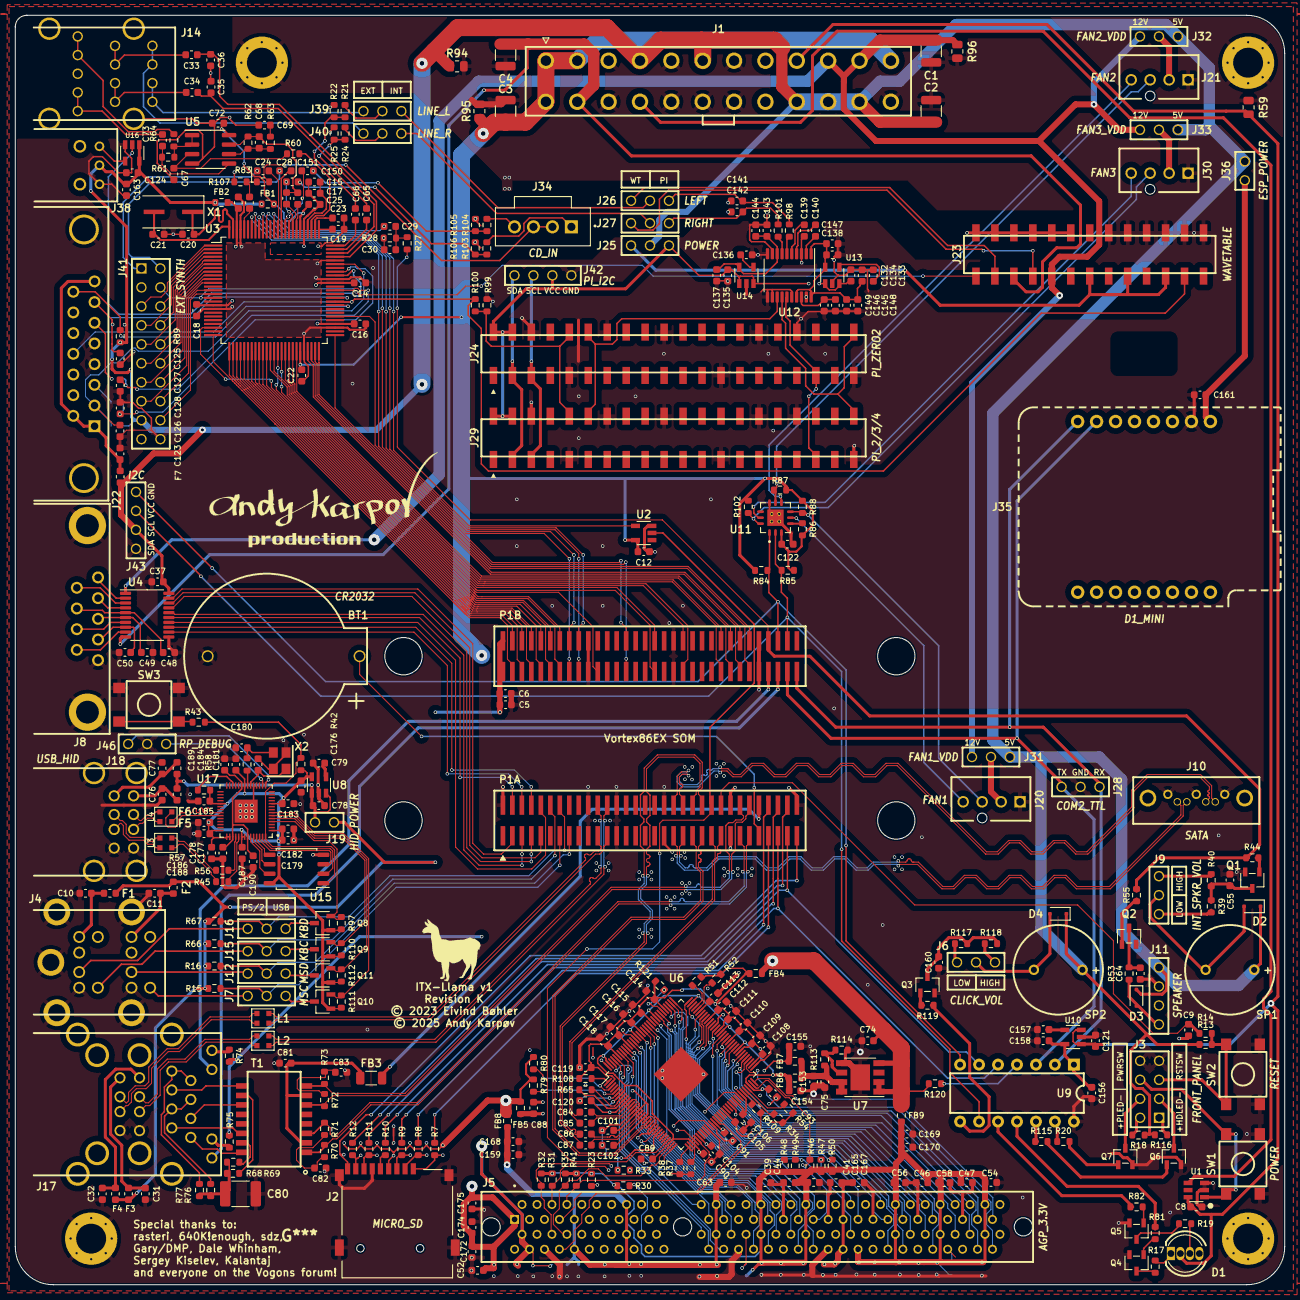
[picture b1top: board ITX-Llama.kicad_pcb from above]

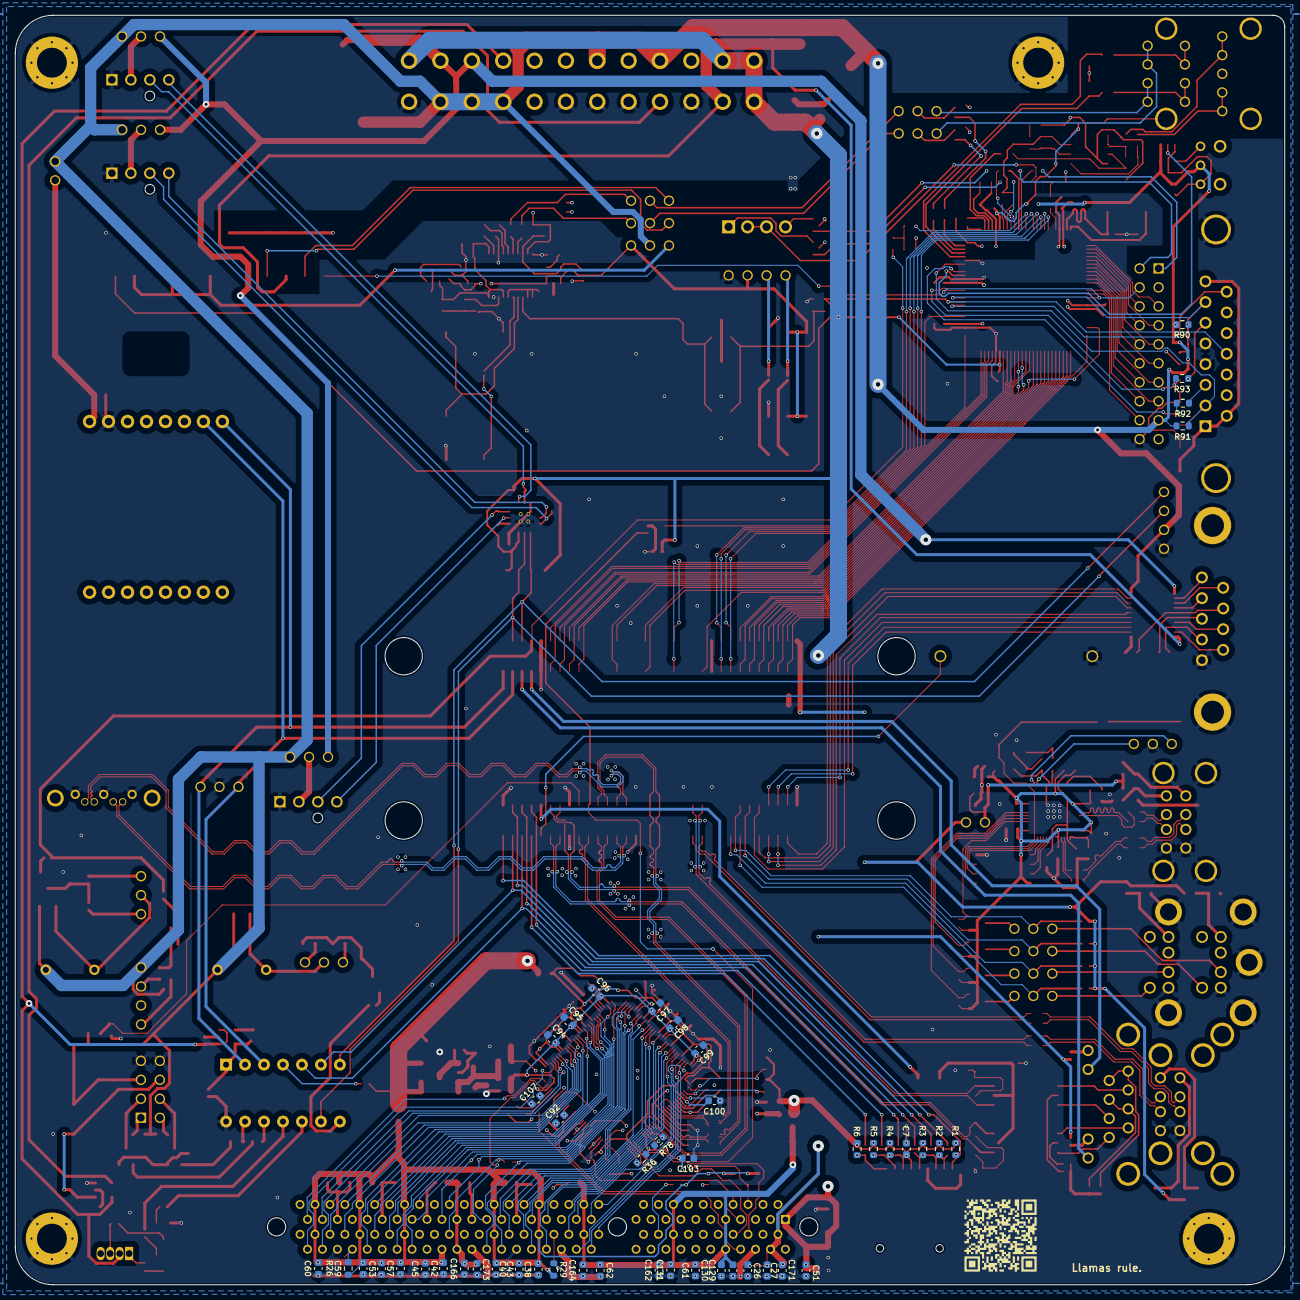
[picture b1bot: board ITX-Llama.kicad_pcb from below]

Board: 4 copper layers, 170.0 x 170.0 mm, 421 parts (47 on the bottom side), 384 nets.

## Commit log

2025-03-02 revK
2025-03-02 removed outdated gerbers

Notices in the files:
kicad/ITX-Llama.kicad_pcb:
© 2023 Eivind Bøhler
© 2025 Andy Karpøv
